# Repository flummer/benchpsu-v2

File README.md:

# Benchtop PSU v2

This is a conversion of an HP DPS-800GB server power supply, into a benchtop supply with connectors more commonly used for electronics and electrical prototyping.

It's designed to be relatively easy to make, and not least easier to assemble, as there are no dangling wires to solder, and the front part can be assembled by itself and then mounted on the PSU. The only modification I have done to the PSU is to remove the retaining clip, simply by opening the case and drilling out the rivet, holding it in place. It's not a critical modification, but I prefered to get rid of it.

## Features

This is a fairly simple conversion, and there are 3 fixed outputs:

- 3.3 V (5 A max)
- 5.0 V (2 A max)
- 12 V (30 A max)

The DPS-800GB PSU can deliver **much** more than 30A on 12 V, but the measuring circuit used for that channel has a max rating of 30A and the traces on the PCB probably also have a limit, though they have been made as wide as posssible to cope with a bit more current.

The screen will display the current draw on each output.

As the 3.3 V and 5.0 V outputs are part of the standby system in the DPS-800GB, they are always on, but the 12 V output is controlled via an optocoupler from the microcontroller, and the firmware is set up so that the single button turns that on and off.

## Notes

When mains power is connected, the fan is **not** running, but the PSU will get a bit warm if it sits like that for some time and it will also draw about 15W just sitting there, which isn't ideal. When the 12 V output is enabled, the fan will kick in, but unless you put a heavy load on it, it will only run slowly and not be super noisy, though it isn't silent in any way.

## Electronics

The electronics is build around an ATmega328p microcontroller and 3 ACS712 current sensors with analog output, and the firmware has some magic numbers for converting the value read from the analog inputs into ampere. Those have been found by putting a few known loads on the PSU and looking at the readings. It's a bit hacky, but good enough for a quick measurement if you just need to know if you are in the ballpark.

The banana connectors are the Pomona 6883 Dual Binding post and they are also used to hold the PCB inside the 3D printed case, and the friction of the connector and the 3D print against the case of the DPS-800GB is enough to keep it together, though the 3D model do have holes that match up with the existing screws of the DPS-800GB.

The card edge connector used to match with the DPS-800GB is an Amphenol FCI 10046971-001LF.

## License

The hardware, firmware, 3D models and artwork in this repository are released under the following license:

* the "Creative Commons Attribution-ShareAlike 4.0 International License"
  (CC BY-SA 4.0) full text of this license is included in the LICENSE file
  and a copy can also be found at
  [http://creativecommons.org/licenses/by-sa/4.0/](http://creativecommons.org/licenses/by-sa/4.0/)

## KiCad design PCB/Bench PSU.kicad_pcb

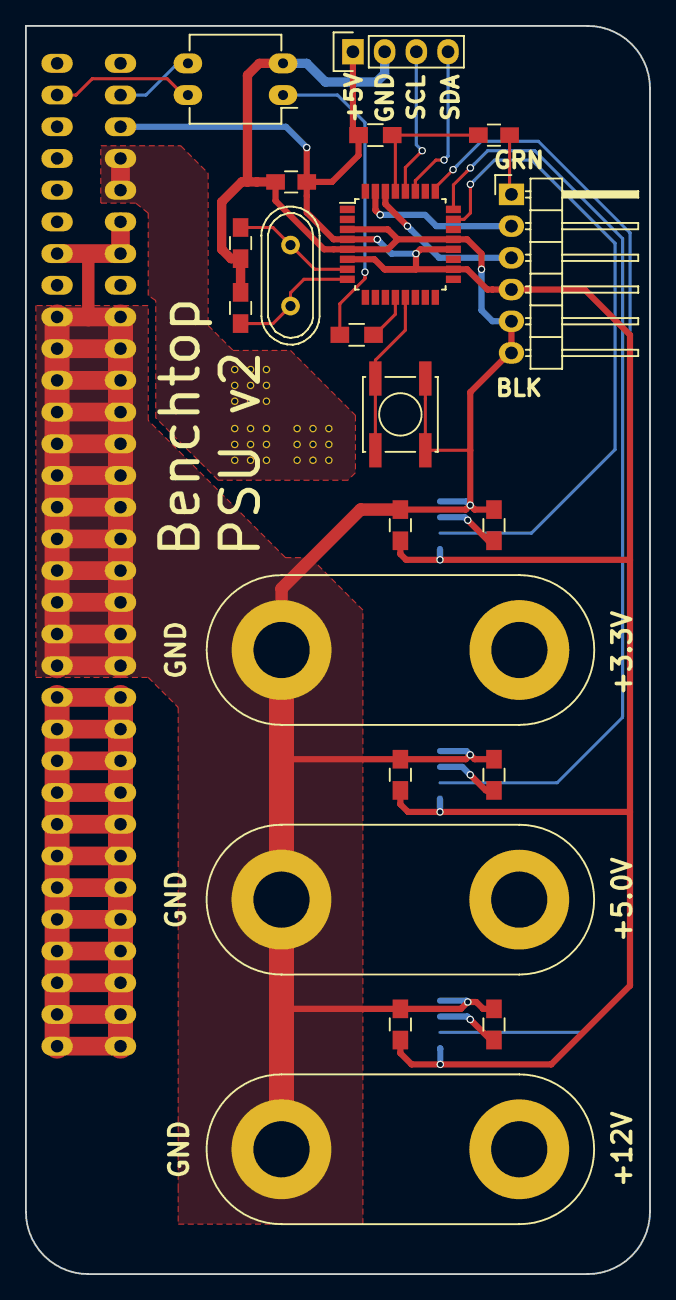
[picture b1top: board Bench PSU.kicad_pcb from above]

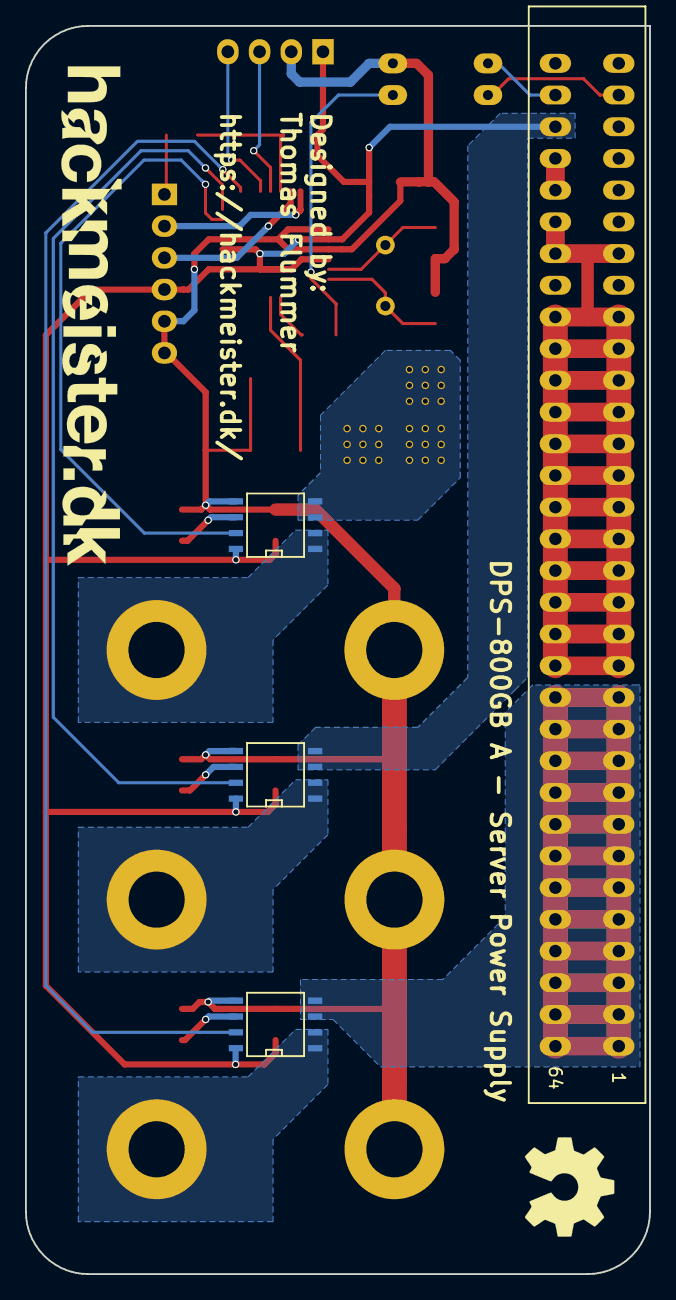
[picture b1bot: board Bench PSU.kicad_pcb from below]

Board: 2 copper layers, 50.0 x 100.0 mm, 25 parts (4 on the bottom side), 26 nets.

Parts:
3v1, 5v1, 12v1: CONN_01X02; DualBindingPost
16MHz1: Crystal; Crystal_HC49-U_Vertical
C1, C2: 1nF; C_0805_HandSoldering
C3, C4, C5, C6, C9: 100nF; C_0805_HandSoldering
C7, C8: 22pF; C_0805_HandSoldering
IC1: ATMEGA328P-A; LQFP-32_7x7mm_Pitch0.8mm
P1: C64AB; 10046971-001LF
P2: CONN_01X04; Pin_Header_Straight_1x04
P3: CONN_01X06; Pin_Header_Angled_1x06
R1: 10K; R_0805_HandSoldering
R2: R; R_0805_HandSoldering
SW1: Switch_DPST; SW_SPST_EVPBF
U1, U2, U3: ACS712; SOIC-8-N
U4: PC817; DIP-4_W7.62mm_LongPads
c1: 1nF; C_0805_HandSoldering

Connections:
3v3_out: 3v1.2, U1.1, U1.2
3v3_sense: IC1.23, U1.7
5v_out: 5v1.2, U2.1, U2.2
5v_sense: IC1.24, U2.7
12v_out: 12v1.2, U3.1, U3.2
12v_sense: IC1.25, U3.7
+3V3: P1.B28, P1.B29, U1.3, U1.4
+5V: C3.1, C4.1, C5.1, C6.1, IC1.4, IC1.6, IC1.18, IC1.20, P1.B30, P2.1, P3.4, R1.2, U1.8, U2.3, U2.4, U2.8, U3.8
+12V: P1.A1, P1.A2, P1.A3, P1.A4, P1.A5, P1.A6, P1.A7, P1.A8, P1.A9, P1.A10, P1.A11, P1.A12, P1.B1, P1.B2, P1.B3, P1.B4, P1.B5, P1.B6, P1.B7, P1.B8, P1.B9, P1.B10, P1.B11, P1.B12, U3.3, U3.4
GND: 3v1.1, 5v1.1, 12v1.1, C1.2, C2.2, C3.2, C4.2, C5.2, C6.2, C7.2, C8.2, IC1.3, IC1.5, IC1.21, P1.A13, P1.A14, P1.A15, P1.A16, P1.A17, P1.A18, P1.A19, P1.A20, P1.A21, P1.A22, P1.A23, P1.A24, P1.A26, P1.B13, P1.B14, P1.B15, P1.B16, P1.B17, P1.B18, P1.B19, P1.B20, P1.B21, P1.B22, P1.B23, P1.B24, P1.B26, P1.B27, P2.2, P3.5, P3.6, SW1.2, U1.5, U2.5, U3.5, U4.2, c1.2
unnamed: 16MHz1.1, C7.1, IC1.7
unnamed: 16MHz1.2, C8.1, IC1.8
unnamed: C1.1, U1.6
unnamed: C2.1, U3.6
unnamed: C9.1, P3.1
unnamed: C9.2, IC1.29, R1.1
unnamed: IC1.12, R2.1
unnamed: IC1.13, SW1.1
unnamed: IC1.30, P3.3
unnamed: IC1.31, P3.2
unnamed: P1.A31, U4.4
unnamed: P1.B31, U4.3
unnamed: R2.2, U4.1
unnamed: U2.6, c1.1
SCL: IC1.28, P2.3
SDA: IC1.27, P2.4

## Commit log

2024-04-07 Added readme, license and photos
2024-04-07 Fixed typo
2024-04-07 Fixed a few more typos
